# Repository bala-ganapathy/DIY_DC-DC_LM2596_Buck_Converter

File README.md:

# DIY DC-DC Buck Converter  
This repository contains the KiCad project files for a DIY DC-DC buck converter designed to step down a higher input voltage to a stable, lower output voltage. It is aimed at providing an efficient power solution for electronic devices requiring a specific operating voltage, such as sensors, microcontrollers, and other low-power devices.

## Project Files  
- **Schematic Diagram**: Attached 
- **PCB Layout**: Attached
## Design Overview  
This DIY DC-DC buck converter uses the **LM2596** IC, which is a highly efficient, adjustable step-down (buck) voltage regulator. The converter can take input voltages ranging from 4V to 40V and efficiently output a fixed lower voltage (such as 5V, 9V, or 12V) to power various electronics. The design is intended for low to medium power applications, with a focus on providing stable output and minimizing power loss.

### Key Features:
- **Adjustable Output Voltage**: The output voltage is adjustable by selecting the appropriate feedback resistors.
- **High Efficiency**: Using the LM2596 ensures high efficiency, typically around 80-90%, minimizing heat generation.
- **Overcurrent Protection**: Built-in protection mechanisms to prevent damage under overload conditions.
- **Compact Design**: The PCB layout is optimized for small form-factor applications, making it suitable for portable devices.

## Components  
| Component         | Value        | Purpose                                    |  
|-------------------|--------------|--------------------------------------------|  
| LM2596            | -            | DC-DC Buck Converter IC                   |  
| C_in1             | 100 µF       | Input Capacitor (for voltage stability)    |  
| C_out1            | 220 µF       | Output Capacitor (for smooth output)       |  
| C_feedback1       | 10 µF        | Feedback Capacitor (stability)             |  
| L1                | 33 µH        | Inductor (energy storage for conversion)   |  
| D1                | 1N5819       | Schottky Diode (for rectification)         |  
| R1                | 1 kΩ         | Feedback Resistor (sets output voltage)    |  
| J_input           | -            | Power Input Connector                      |  
| J_output          | -            | Power Output Connector                     |  

## Notes  
- **Voltage Adjustment**: The output voltage is adjustable by changing the feedback resistors (R1) according to the desired output voltage formula provided in the LM2596 datasheet.
- **Thermal Considerations**: The LM2596 operates efficiently, but it is still important to ensure good thermal management, especially at higher input voltages or current draws.
- **Simulation**: Currently, this design has not been simulated, so real-world testing is essential to ensure performance under various conditions.
- **No Ground Pin**: The J_ground pin is not used in this design, as the ground connection is directly routed to the PCB.

## Design Goals  
This project aims to deliver a compact and reliable power supply solution suitable for applications where high efficiency and stable voltage are essential. The converter is ideal for powering small electronics, Arduino projects, sensors, and other low-power devices requiring regulated power.

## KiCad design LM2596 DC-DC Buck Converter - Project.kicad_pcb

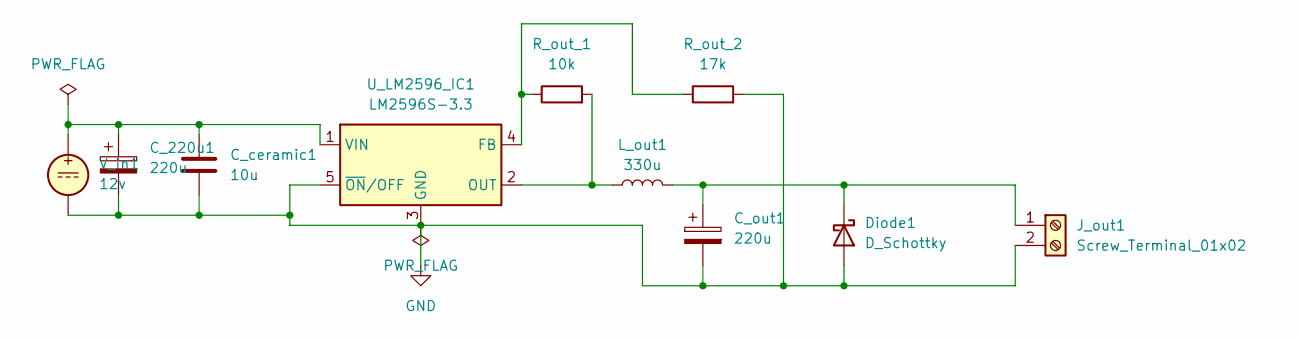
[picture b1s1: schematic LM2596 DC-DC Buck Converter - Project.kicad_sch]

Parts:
C_220u1: 220u; CP_Radial_D8.0mm_P3.50mm
C_ceramic1: 10u; C_1206_3216Metric
C_out1: 220u; CP_Radial_D8.0mm_P3.50mm
Diode1: D_Schottky; D_DO-201AD_P15.24mm_Horizontal
J_out1: Screw_Terminal_01x02; PinHeader_1x02_P1.00mm_Vertical
L_out1: 330u; L_Radial_D10.0mm_P5.00mm_Fastron_07M
R_out_1: 10k; R_Axial_DIN0207_L6.3mm_D2.5mm_P10.16mm_Horizontal
R_out_2: 17k; R_Axial_DIN0207_L6.3mm_D2.5mm_P10.16mm_Horizontal
U_LM2596_IC1: LM2596S-3.3; TO-263-5_TabPin3
V_in1: 12v; PinHeader_1x02_P1.00mm_Vertical

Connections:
GND: C_220u1.2, C_ceramic1.2, C_out1.2, Diode1.2 (A), J_out1.2, R_out_2.2, U_LM2596_IC1.3 (GND), U_LM2596_IC1.5 (~ON/OFF), V_in1.2
unnamed: C_out1.1, Diode1.1 (K), J_out1.1, L_out1.2
unnamed: R_out_1.1, R_out_2.1, U_LM2596_IC1.4 (FB)
unnamed: L_out1.1, R_out_1.2, U_LM2596_IC1.2 (OUT)
unnamed: C_220u1.1, C_ceramic1.1, U_LM2596_IC1.1 (VIN), V_in1.1

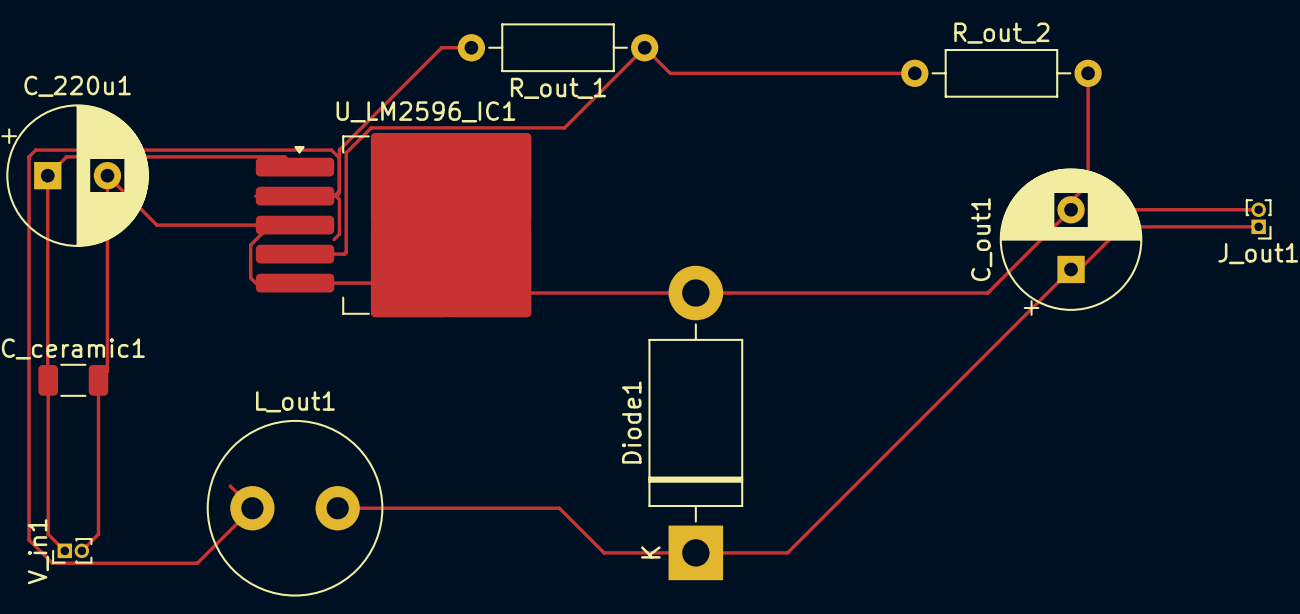
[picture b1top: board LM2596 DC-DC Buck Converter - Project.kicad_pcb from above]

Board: 2 copper layers, 10 parts (0 on the bottom side), 5 nets.
